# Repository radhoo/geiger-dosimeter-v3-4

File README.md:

# geiger-dosimeter-v3-4

Given all my previous experience with Geiger Counters (see the uRADMonitor project, http://www.uradmonitor.com 
), I have decided to conceive a portable, easy to build, radiation dosimeter. 
I didn't have much need for yet another dosimeter (with my Radex 1706 or Terra-P), but I know there are several 
people not affording a commercial unit, but wanting to have their own radiation measurement tool. So here is this project, 
giving you just that: an efficient, stable, easy to build construction for all your radiation dosimetry needs.

Short description
I've started from scratch, designing a complete dosimeter unit around the Atmel Atmega8 microcontroller and a Russian 
Geiger Muller tube. Here you'll see the STS-1 tube, for high gamma doses, but the dosimeter can be used with any other 
tubes such as SBM-20, LND-712 or more sensitive ones such as the SBM-19 or the pancake tube SI-14B. Changing the tube 
requires changing the software, to adjust the dose conversion calculation. This circuit can be used with almost any geiger 
tube, as even the inverter's output voltage driving the tube is adjustable in the software.

I've been invited to show this dosimeter on a TV Show, on TVR Timisoara (video is in Romanian):
http://www.youtube.com/watch?v=WXmPR-FNbIg

Functionality
Similar to my uRADMonitor, the microcontroller takes care of everything:
1. Generates a variable duty PWM signal using Timer1, to drive the 400V inverter needed to operate the Geiger tube; 
The invertor doesn't need a multiplier, as the ferrite's transformer secondary puts out exactly the amount required. 
The transformer is made on a A22 ferrite core, with 16 turns in the primary and 600 in the secondary.
2. Uses one ADC port to measure the inverter's voltage and adjust the PWM duty cycle for constant output 
(exactly 400V for stable operation)
3. Counts the time, using Timer0 so we can compute the dose
4. Uses interrupt INT0 to count the pulses produced by the Geiger tube
5. Drives a 2x16 LCD to output the results.
Some other circuits on the Internet come with improper 400V inverters (some people seem not to be able to design a 
proper inverter), they are redundant (using 555's and additional components, when the microcontroller can take care 
of EVERYTHING), use the wrong signal detection/counter circuit, or other small defects that result in wrong measurements. 
Not to mention the controversial aspect of computing dose in sieverts out of counts per minute.
Given all the wrong designs out there, my detector tries to fill in some of the gaps. So here is exactly what you need: 
a stable design, with several improvements made over time, all packed in this nice construction that you can easily replicate.

More on http://www.pocketmagic.net/?p=3342 

Circuit diagram
http://www.pocketmagic.net/wp-content/uploads/2012/12/geiger_counter_schematics.png

License
This work is free software, licensed under GPL v2; you can redistribute it and/or modify it under the terms of the GNU General 
Public License as published by the Free Software Foundation; either version 2 of the License, or (at your option) any later 
version. For other licensing options, feel free to contact me. 

Additional resources

More details available on my blog: http://www.pocketmagic.net/?p=3342

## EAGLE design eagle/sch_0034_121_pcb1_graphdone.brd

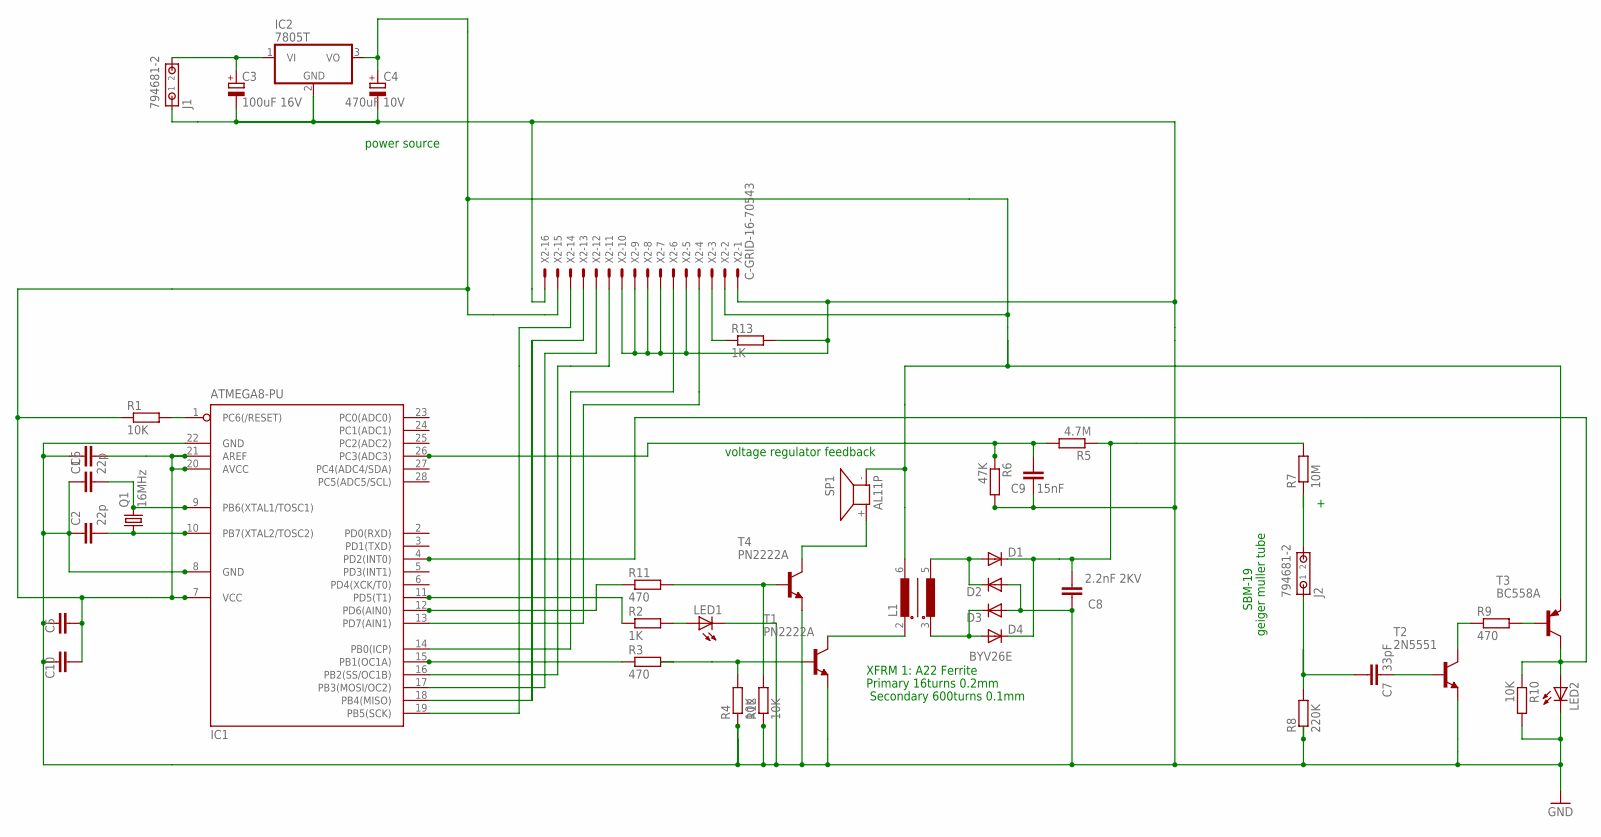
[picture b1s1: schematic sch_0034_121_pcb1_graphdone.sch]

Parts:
C1, C2: 22p; C025-024X044
C3: 100uF 16V; E2,5-6E
C4: 470uF 10V; E2,5-6E
C5, C6, C10: 100nF; C025-024X044
C7: 33pF; C025-024X044
C8: 2.2nF 2KV; C025-024X044
C9: 15nF; C025-024X044
D1, D2, D3: DIODE-D-7.5; D-7.5
D4: BYV26E; D-7.5
IC1: ATMEGA8-PU; DIL28-3
IC2: 7805T; TO220H
J1, J2: 794681-2
L1: RM6-2; RM5-4
LED1, LED2: LED3MM
Q1: 16MHz; HC49U-V
R1, R4, R10, R12: 10K; 0204/7
R2, R13: 1K; 0204/7
R3, R9, R11: 470; 0204/7
R5: 4.7M; 0204/7
R6: 47K; 0204/7
R7: 10M; 0204/7
R8: 220K; 0204/7
SP1: AL11P
T1, T4: PN2222A; TO92-EBC
T2: 2N5551; TO92-EBC
T3: BC558A; TO92-EBC
X2: C-GRID-16-70543; 70543-16

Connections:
GND: C1.1, C2.1, C3.-, C4.-, C5.2, C6.2, C8.1, C9.1, C10.2, D2.A, D3.A, IC1.8 (GND), IC1.22 (GND), IC2.2 (GND), J1.1, LED1.K (C), LED2.K (C), R4.1, R6.2, R8.1, R10.2, R12.1, R13.2, T1.E, T2.E, T4.E, X2.1, X2.5, X2.7, X2.8, X2.9, X2.10, X2.16
unnamed: C1.2, IC1.9 (PB6(XTAL1/TOSC1)), Q1.2
unnamed: C2.2, IC1.10 (PB7(XTAL2/TOSC2)), Q1.1
unnamed: IC1.18 (PB4(MISO)), X2.13
unnamed: IC1.11 (PD5(T1)), R2.1
unnamed: R3.2, R4.2, T1.B
unnamed: SP1.+ (2), T4.C
unnamed: C4.+, C5.1, C6.1, C10.1, IC1.7 (VCC), IC1.20 (AVCC), IC1.21 (AREF), IC2.3 (VO), L1.6 (W1E), R1.1, SP1.- (1), T3.E, X2.2, X2.15
unnamed: IC1.12 (PD6(AIN0)), R11.1
unnamed: R11.2, R12.2, T4.B
unnamed: LED1.A, R2.2
unnamed: C3.+, IC2.1 (VI), J1.2
unnamed: L1.2 (W1A), T1.C
unnamed: C7.2, J2.1, R8.2
unnamed: D3.C, D4.A, L1.3 (W2A)
unnamed: D1.A, D2.C, L1.5 (W2E)
unnamed: C7.1, T2.B
unnamed: C8.2, D1.C, D4.C, R5.1, R7.2
unnamed: C9.2, IC1.26 (PC3(ADC3)), R5.2, R6.1
unnamed: J2.2, R7.1
unnamed: R9.1, T2.C
unnamed: R9.2, T3.B
unnamed: IC1.4 (PD2(INT0)), LED2.A, R10.1, T3.C
unnamed: IC1.13 (PD7(AIN1)), X2.4
unnamed: IC1.1 (PC6(/RESET)), R1.2
unnamed: IC1.15 (PB1(OC1A)), R3.1
unnamed: IC1.19 (PB5(SCK)), X2.14
unnamed: IC1.17 (PB3(MOSI/OC2)), X2.12
unnamed: R13.1, X2.3
unnamed: IC1.14 (PB0(ICP)), X2.6
unnamed: IC1.16 (PB2(SS/OC1B)), X2.11

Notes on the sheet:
XFRM 1: A22 Ferrite
Primary 16turns 0.2mm
Secondary 600turns 0.1mm
voltage regulator feedback
geiger muller tube
power source
SBM-19

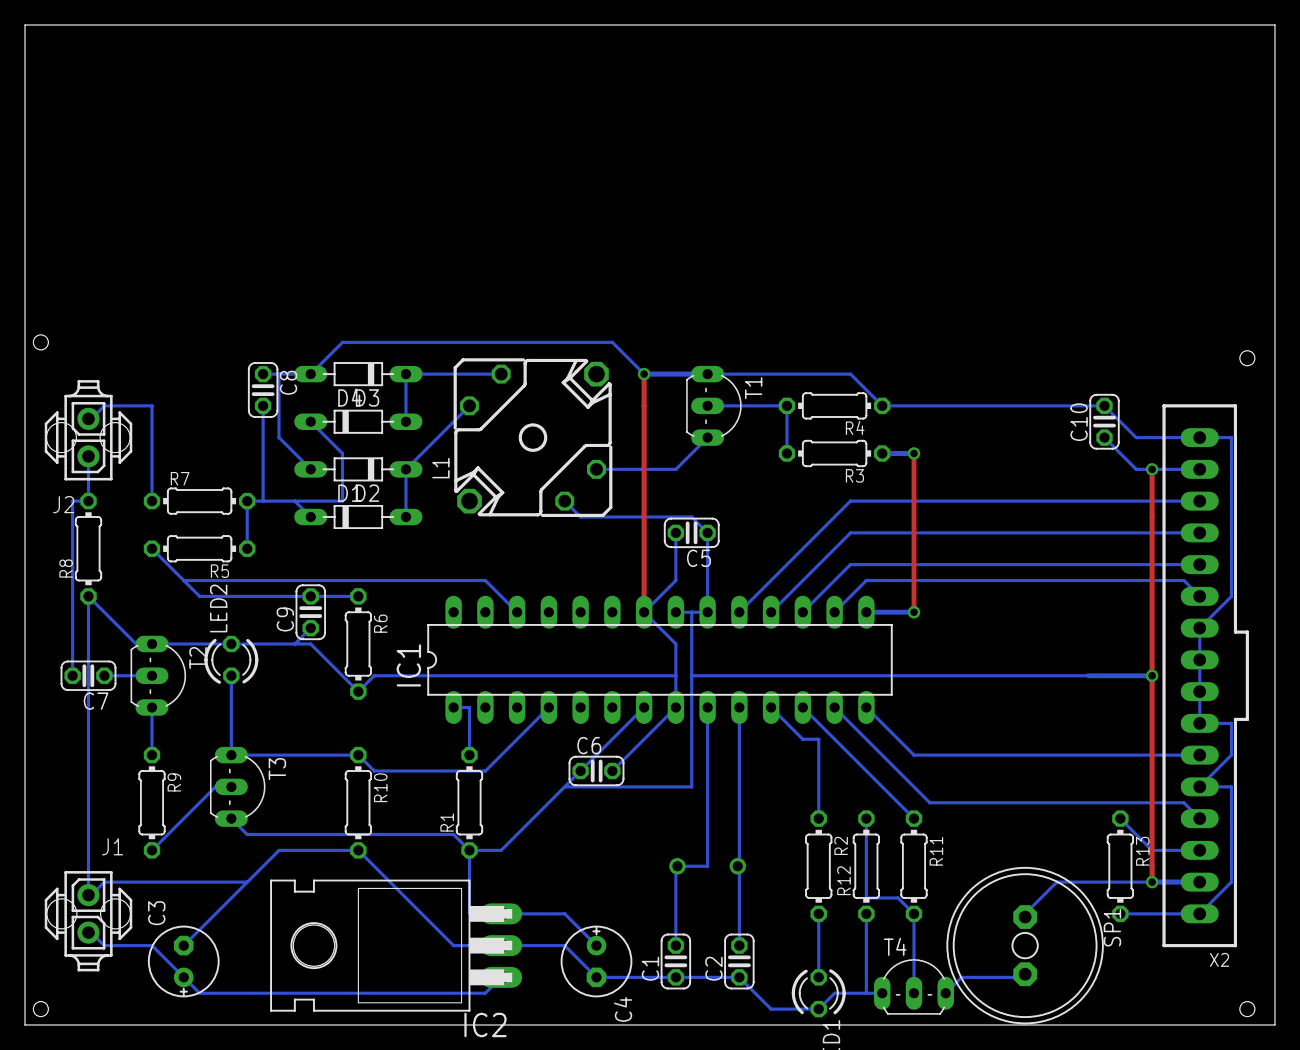
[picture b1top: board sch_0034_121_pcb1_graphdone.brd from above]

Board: 2 copper layers, 100.0 x 80.0 mm, 41 parts (1 on the bottom side), 31 nets.

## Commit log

2013-05-26 version 3.4.121.A
2015-04-27 Migrating wiki contents from Google Code
2016-04-25 ported to eclipse, fixed default duty cycle, pulse length and refresh mechanism
2016-04-25 added gitignore
